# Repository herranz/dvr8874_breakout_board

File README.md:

<div align="center">

  <h1>DVR8874 breakout board </h1>
  <p> Simple breakout board to use the DVR8874 in prototypes </p>

<!-- Badges -->

<h4>
    <a href="https://bsky.app/profile/herranz.bsky.social">BLUESKY</a>
  <span> · </span>
    <a href="https://www.github.com/herranz">GITHUB</a>
  
  </h4>

</div>

<br />

<div>&nbsp;</div>

## Table of Contents
* [General Info](#general-information)
* [Screenshots](#screenshots)
* [Setup](#setup)
* [Usage](#usage)
* [Project Status](#project-status)
* [Acknowledgements](#acknowledgements)
* [Contact](#contact)
* [License](#license)

## General Information
- This is a simple breakout board designed to facilitate the use of the DVR8874 motor driver in prototype designs. The board provides easy access to all essential pins of the DVR8874, allowing quick testing of its capabilities.
<!-- You don't have to answer all the questions - just the ones relevant to your project. -->

<!--
## Technologies Used
- Tech 1 - version 1.0
- Tech 2 - version 2.0
- Tech 3 - version 3.0

## Features
List the ready features here:
- Awesome feature 1
- Awesome feature 2
- Awesome feature 3

-->
## Screenshots

## Setup

The board was ordered through [JLCPCB](https://www.jlcpcb.com). No special restrictions or construction is required.

## Usage
Recomend read the datasheet of the [DVR8874](https://www.ti.com/product/DRV8874)

## Project Status
Project is: __COMPLETE__ 

<!--## Room for Improvement
Include areas you believe need improvement / could be improved. Also add TODOs for future development.

Room for improvement:
- Improvement to be done 1
- Improvement to be done 2

To do:
- Feature to be added 1
- Feature to be added 2
-->

## Acknowledgements
- No ACK today.

## Contact
Created by [@herranz]- feel free to contact me!

 ## License 
 This project is open source and available under the [... License]().

 You don't have to include all sections - just the one's relevant to your project

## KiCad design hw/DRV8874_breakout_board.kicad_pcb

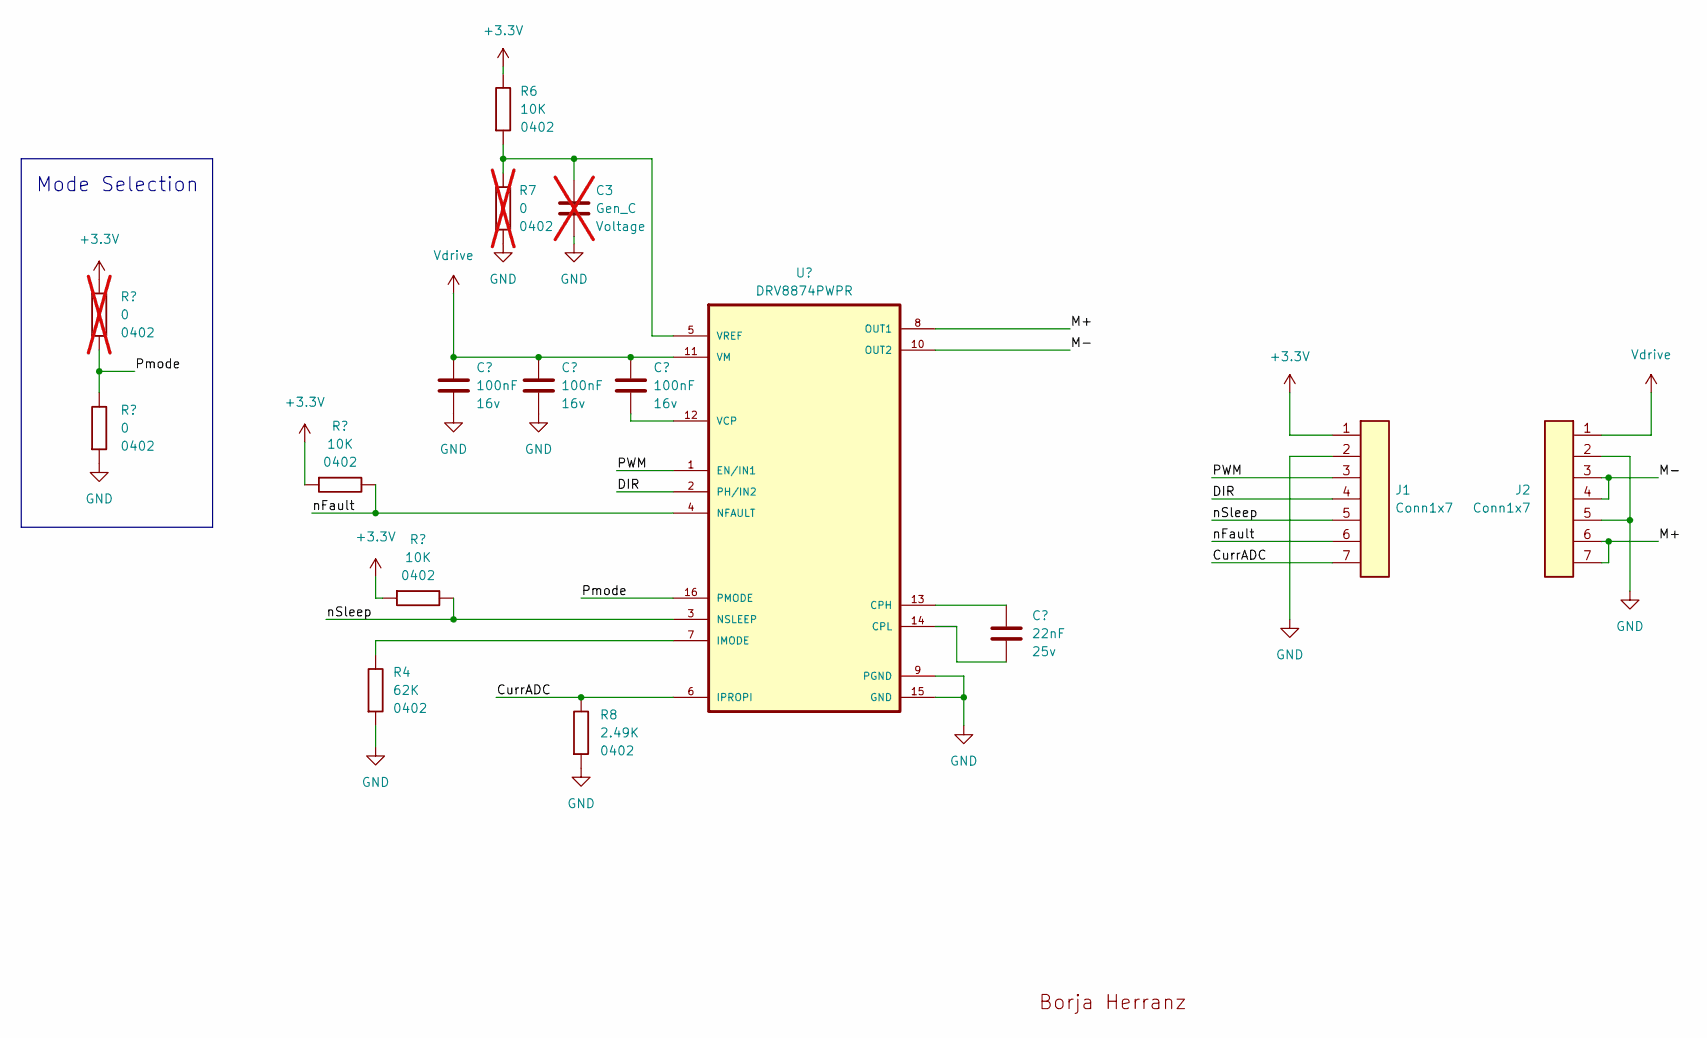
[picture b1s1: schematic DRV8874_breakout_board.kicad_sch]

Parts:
C1, C2, C4: 100nF; C_0603_1608Metric; Voltage 16v; LCSC C66501
C3: Gen_C; C_0402_1005Metric; Voltage Voltage; not fitted
C5: 22nF; C_0603_1608Metric; Voltage 25v; LCSC C779971
J1, J2: Conn1x7; PinHeader_1x07_P2.54mm_Vertical
R1: 0; R_0402_1005Metric; LCSC C4044221; not fitted
R2: 0; R_0402_1005Metric; LCSC C4044221
R3, R5, R6: 10K; R_0402_1005Metric; LCSC C163478
R4: 62K; R_0402_1005Metric; LCSC C137950
R7: 0; R_0402_1005Metric; not fitted
R8: 2.49K; R_0402_1005Metric; LCSC C145071
U1: DRV8874PWPR; SOP65P640X120-17N; LCSC C1855818
U2: Logo_Small; LOGO_small

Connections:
+3V3: J1.1, R1.2, R3.1, R5.1, R6.2
/CurrADC: J1.7, R8.2, U1.6 (IPROPI)
/DIR: J1.4, U1.2 (PH/IN2)
/M+: J2.6, J2.7, U1.8 (OUT1)
/M-: J2.3, J2.4, U1.10 (OUT2)
/PWM: J1.3, U1.1 (EN/IN1)
/Pmode: R1.1, R2.2, U1.16 (PMODE)
/nFault: J1.6, R3.2, U1.4 (NFAULT)
/nSleep: J1.5, R5.2, U1.3 (NSLEEP)
GND: C1.2, C2.2, C3.2, J1.2, J2.2, J2.5, R2.1, R4.1, R7.1, R8.1, U1.9 (PGND), U1.15 (GND)
unnamed: C5.1, U1.13 (CPH)
unnamed: C5.2, U1.14 (CPL)
unnamed: R4.2, U1.7 (IMODE)
unnamed: C4.2, U1.12 (VCP)
unnamed: C3.1, R6.1, R7.2, U1.5 (VREF)
Vdrive: C1.1, C2.1, C4.1, J2.1, U1.11 (VM)

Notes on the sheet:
Mode Selection

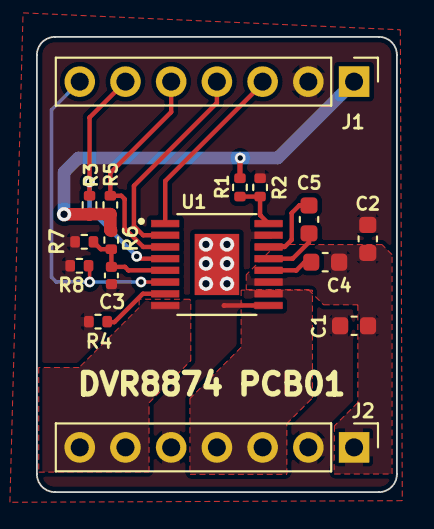
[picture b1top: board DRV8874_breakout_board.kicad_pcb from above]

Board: 2 copper layers, 20.0 x 25.3 mm, 17 parts (1 on the bottom side), 16 nets.

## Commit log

2023-11-21 Forma de PCB con espacios para tira de pines
2023-11-22 primera iteración PCB
2023-11-29 Añadido divisor de resistencia para v_ref
2023-12-01 sanity push
2023-12-01 añadidos LCSC y archivos de produccion
2024-12-19 Cleanup
2024-12-20 Update README.md
    readme clean up

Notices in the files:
hw/DRV8874_breakout_board.kicad_pcb:
CERN-OHL-W
